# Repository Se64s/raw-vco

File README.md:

# raw-vco

Eurorack VCO module based in EDU DIY VCO from erica synth and Moritz Klein.

# About the project

This is the first module of the series 'RAW'.

The RAW concept is my way to ease access to the modular world, reducing the cost of the modules to the minimum, removing all unnecessary parts without scarify functionality.

In this case, I took the awesome design of Moritz, but I removed the fancy faceplate and I added a saw-triangle converter to have all the basic waveforms.

# Module overview

## Inputs

- lineal fm cv input.
- pwm cv control input.
- 1v/oct control input (good tracking over 5 octaves).

## Outputs

### Triagle

### Saw

### Square

# Acknowledgments

All design and guts of this module were done by Moritz Klein so I recommend visiting his awesome videos to get a precise idea of how this module works.

- [mki x es.EDU](https://www.ericasynths.lv/news/mki-x-esedu/)

# Contact

Any feedback is welcome!
- Sebastián Del Moral - sebmorgal@gmail.com

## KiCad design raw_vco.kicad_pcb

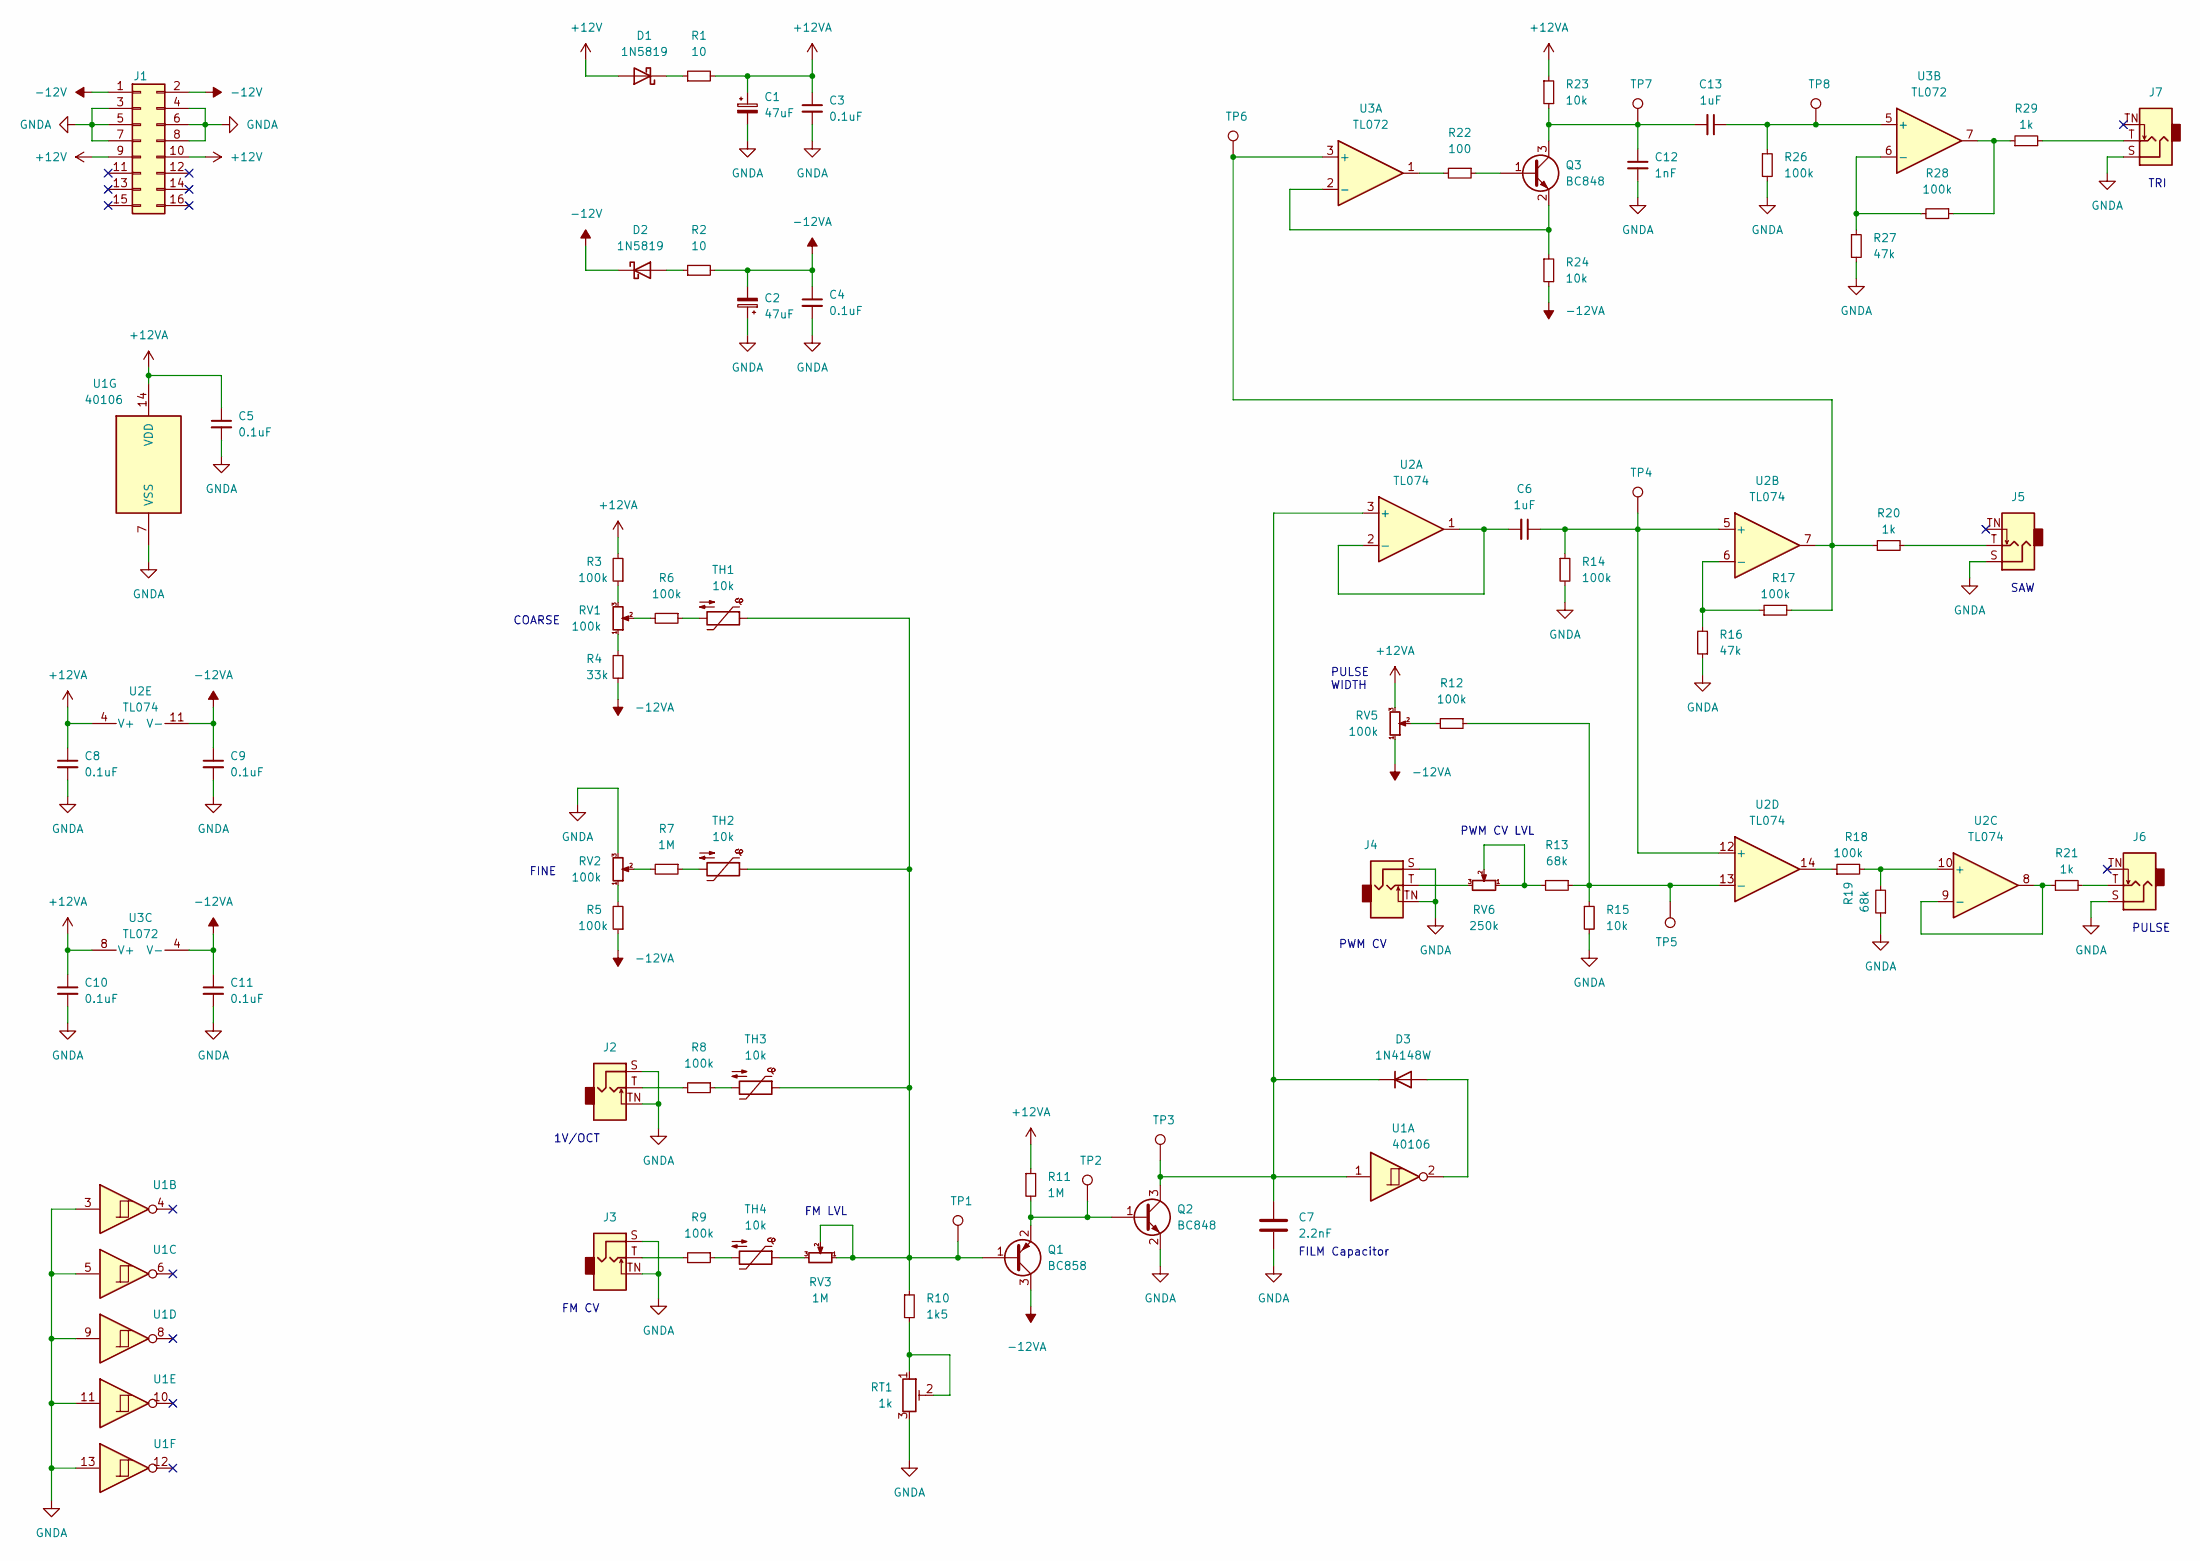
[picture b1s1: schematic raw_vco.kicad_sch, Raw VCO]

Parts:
C1, C2: 47uF; CP_Elec_6.3x5.4
C3, C4, C5, C8, C9, C10, C11: 0.1uF; C_0603_1608Metric_Pad1.08x0.95mm_HandSolder
C6, C13: 1uF; C_0603_1608Metric_Pad1.08x0.95mm_HandSolder
C7: 2.2nF; C_Rect_L7.0mm_W2.0mm_P5.00mm
C12: 1nF; C_0603_1608Metric_Pad1.08x0.95mm_HandSolder
D1, D2: 1N5819; D_SOD-123
D3: 1N4148W; D_SOD-123
J1: Conn_02x08_Odd_Even; PinHeader_2x08_P2.54mm_Vertical_SMD
J2, J3, J4, J5, J6, J7: AudioJack2_SwitchT; Jack_3.5mm_QingPu_WQP-PJ398SM_Vertical_CircularHoles
Q1: BC858; SOT-23
Q2, Q3: BC848; SOT-23
R1, R2: 10; R_0805_2012Metric_Pad1.20x1.40mm_HandSolder
R3, R5, R6, R8, R9, R12, R14, R17, R18, R26, R28: 100k; R_0603_1608Metric_Pad0.98x0.95mm_HandSolder
R4: 33k; R_0603_1608Metric_Pad0.98x0.95mm_HandSolder
R7, R11: 1M; R_0603_1608Metric_Pad0.98x0.95mm_HandSolder
R10: 1k5; R_0603_1608Metric_Pad0.98x0.95mm_HandSolder
R13, R19: 68k; R_0603_1608Metric_Pad0.98x0.95mm_HandSolder
R15, R23, R24: 10k; R_0603_1608Metric_Pad0.98x0.95mm_HandSolder
R16, R27: 47k; R_0603_1608Metric_Pad0.98x0.95mm_HandSolder
R20, R21, R29: 1k; R_0603_1608Metric_Pad0.98x0.95mm_HandSolder
R22: 100; R_0603_1608Metric_Pad0.98x0.95mm_HandSolder
RT1: 1k; Potentiometer_Bourns_3296W_Vertical
RV1, RV2, RV5: 100k; Potentiometer_Alpha_RD901F-40-00D_Single_Vertical
RV3: 1M; Potentiometer_Alpha_RD901F-40-00D_Single_Vertical
RV6: 250k; Potentiometer_Alpha_RD901F-40-00D_Single_Vertical
TH1, TH2, TH3, TH4: 10k; R_Axial_DIN0204_L3.6mm_D1.6mm_P2.54mm_Vertical
TP1, TP2, TP3, TP4, TP5, TP6, TP7, TP8: TestPoint; TestPoint_Pad_D1.5mm
U1: 40106; SOIC-14_3.9x8.7mm_P1.27mm
U2: TL074; SOIC-14_3.9x8.7mm_P1.27mm
U3: TL072; SOIC-8_3.9x4.9mm_P1.27mm

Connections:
+12V: D1.2 (A), J1.9, J1.10
+12VA: C1.1, C3.1, C5.1, C8.1, C10.1, R1.2, R3.2, R11.1, R23.1, RV5.3, U1.14 (VDD), U2.4 (V+), U3.8 (V+)
-12V: D2.1 (K), J1.1, J1.2
-12VA: C2.2, C4.1, C9.1, C11.1, Q1.3 (C), R2.2, R4.1, R5.1, R24.2, RV5.1, U2.11 (V-), U3.4 (V-)
GNDA: C1.2, C2.1, C3.2, C4.2, C5.2, C7.2, C8.2, C9.2, C10.2, C11.2, C12.2, J1.3, J1.4, J1.5, J1.6, J1.7, J1.8, J2.S, J2.TN, J3.S, J3.TN, J4.S, J4.TN, J5.S, J6.S, J7.S, Q2.2 (E), R14.2, R15.2, R16.1, R19.1, R26.2, R27.2, RT1.3, RV2.3, U1.3, U1.5, U1.7 (VSS), U1.9, U1.11, U1.13
unnamed: C6.1, R14.1, TP4.1, U2.5 (+), U2.12 (+)
unnamed: C6.2, U2.1, U2.2 (-)
unnamed: C7.1, D3.1 (K), Q2.3 (C), TP3.1, U1.1, U2.3 (+)
unnamed: C12.1, C13.2, Q3.3 (C), R23.2, TP7.1
unnamed: C13.1, R26.1, TP8.1, U3.5 (+)
unnamed: D1.1 (K), R1.1
unnamed: D2.2 (A), R2.1
unnamed: D3.2 (A), U1.2
unnamed: J2.T, R8.2
unnamed: J3.T, R9.2
unnamed: J4.T, RV6.3
unnamed: J5.T, R20.2
unnamed: J6.T, R21.2
unnamed: J7.T, R29.2
unnamed: Q1.1 (B), R10.1, RV3.1, RV3.2, TH1.1, TH2.1, TH3.1, TP1.1
unnamed: Q1.2 (E), Q2.1 (B), R11.2, TP2.1
unnamed: Q3.1 (B), R22.1
unnamed: Q3.2 (E), R24.1, U3.2 (-)
unnamed: R3.1, RV1.3
unnamed: R4.2, RV1.1
unnamed: R5.2, RV2.1
unnamed: R6.1, TH1.2
unnamed: R7.1, TH2.2
unnamed: R7.2, RV2.2
unnamed: R8.1, TH3.2
unnamed: R9.1, TH4.2
unnamed: R10.2, RT1.1, RT1.2
unnamed: R12.1, R13.1, R15.1, TP5.1, U2.13 (-)
unnamed: R12.2, RV5.2
unnamed: R13.2, RV6.1, RV6.2
unnamed: R16.2, R17.1, U2.6 (-)
unnamed: R17.2, R20.1, TP6.1, U2.7, U3.3 (+)
unnamed: R18.1, U2.14
unnamed: R18.2, R19.2, U2.10 (+)
unnamed: R21.1, U2.8, U2.9 (-)
unnamed: R22.2, U3.1
unnamed: R27.1, R28.2, U3.6 (-)
unnamed: R28.1, R29.1, U3.7
unnamed: R6.2, RV1.2
unnamed: RV3.3, TH4.1

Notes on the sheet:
FILM Capacitor
PWM CV
TRI
COARSE
PWM CV LVL
FINE
SAW
PULSE
1V/OCT
FM LVL
FM CV
PULSE WIDTH

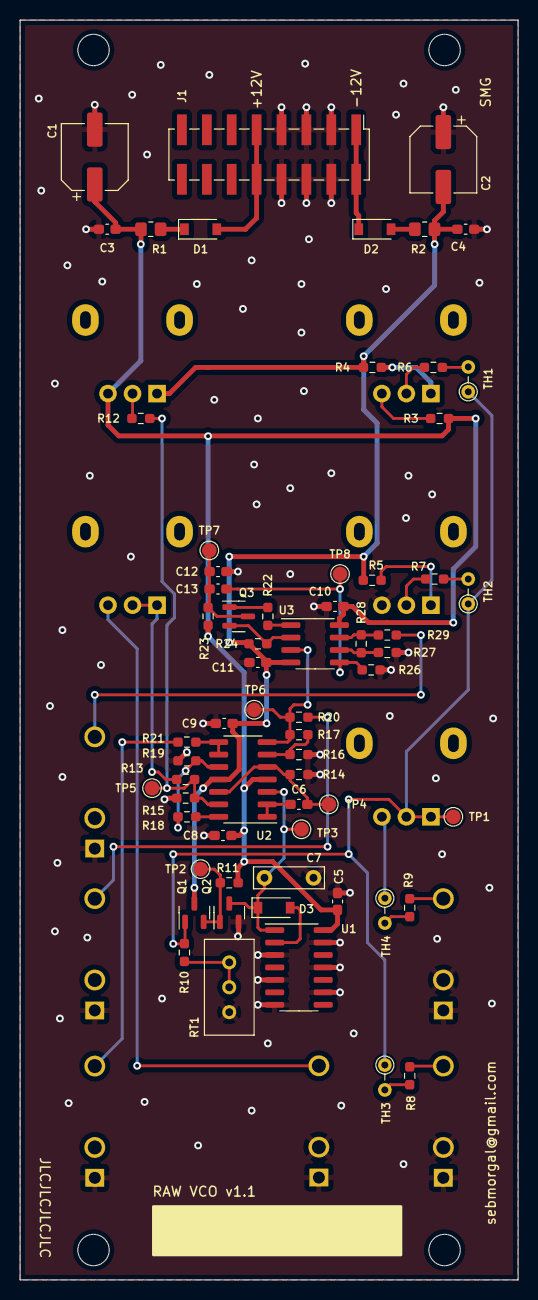
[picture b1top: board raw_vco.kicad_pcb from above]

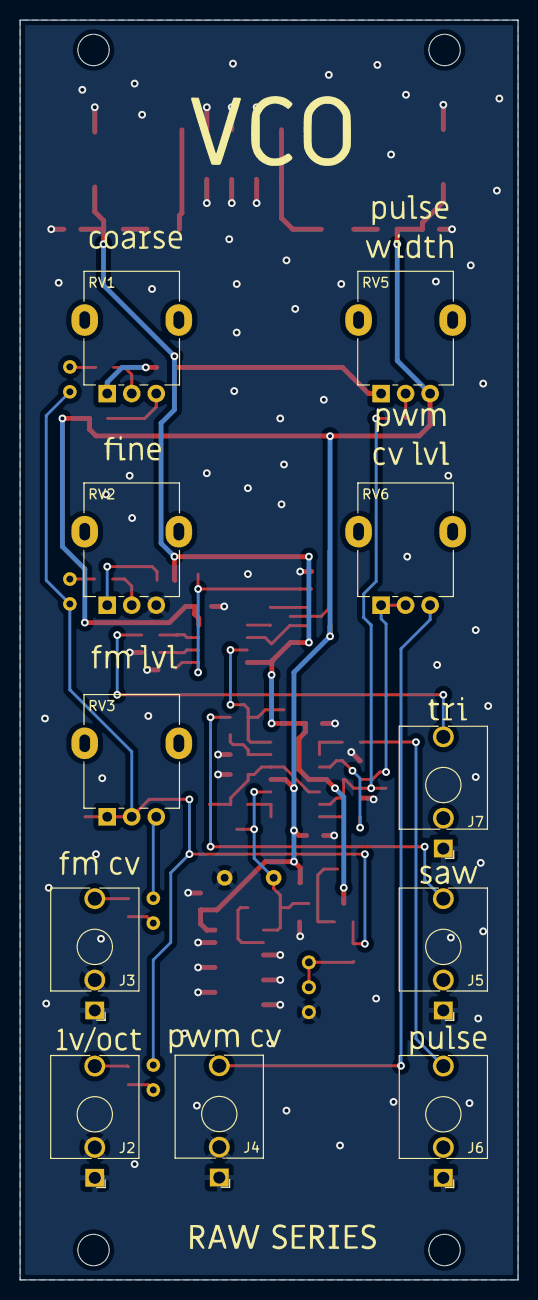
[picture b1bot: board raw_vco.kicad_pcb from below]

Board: 2 copper layers, 50.8 x 128.5 mm, 75 parts (11 on the bottom side), 45 nets.

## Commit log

2022-03-09 [ADD] First commit with board version 1.1
2022-03-13 [ADD] Extend readme info.
